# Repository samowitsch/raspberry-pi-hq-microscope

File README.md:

# Raspberry Pi HQ microscope

> Current work in progress. Feel free to contribute 😉

## Table of Contents

- [Raspberry Pi HQ microscope](#raspberry-pi-hq-microscope)
  - [Table of Contents](#table-of-contents)
  - [Preface](#preface)
  - [PCB adapter or mount between RPI 3A+ and RPI HQ camera](#pcb-adapter-or-mount-between-rpi-3a-and-rpi-hq-camera)
    - [PCB images](#pcb-images)
    - [Available buttons](#available-buttons)
  - [BOM](#bom)
  - [Software](#software)
    - [SD Card](#sd-card)
    - [Install needed packages](#install-needed-packages)
    - [Cronjobs](#cronjobs)
      - [list running cronjobs](#list-running-cronjobs)
      - [stop running cronjonb process](#stop-running-cronjonb-process)
    - [Python](#python)
  - [Links to other projects or resources](#links-to-other-projects-or-resources)
  - [Videos](#videos)
  - [more pictures](#more-pictures)

## Preface

A small project to build a custom electro microscope based on a Raspberr Pi 3A+ and Raspberry HQ camera. 
But why a 3A+? Because of current delivery problems. The 3A+ has also a normal HDMI port and not such an
fiddly diddly micro hdmi port 😜 Also the form factor and the geekworm case is a good choice.
In fact that it based on a Raspberry Pi it can be modified in any direction.

|                        |                        |
| ---------------------- | ---------------------- |
|  |  |
|  |  |

## PCB adapter or mount between RPI 3A+ and RPI HQ camera

The [pcb](pcb/README.md) acts as mounting adapter between the Raspberry Pi 3A+ and the Raspberry Pi HQ Camera. 
It has also 5 buttons that can be used to add custom functions with python.

### PCB images

| Front                             | Back                             |
| --------------------------------- | -------------------------------- |
|  |  |

### Available buttons

| Button | GPIO | Function              |
| ------ | ---- | --------------------- |
| 1      | 17   | select mode/option    |
| 2      | 27   | increase option value |
| 3      | 22   | decrease option value |
| 4      | 19   | capture photo         |
| 5      | 26   | shutdown raspi        |

## BOM

| Part                                                | Quantity     | Description                                                    |
| --------------------------------------------------- | :----------- | -------------------------------------------------------------- |
|                  | 1            | Raspberry Pi 3A+                                               |
|    | 1            | [Geekworm Raspberry pi case](http://wiki.geekworm.com/P88)     |
|                | 1            | Raspberry Pi HQ camera                                         |
|             | 1            | camera cable 6 cm                                              |
|  | 1            | 180x zoom objective with c-mount                               |
|             | 1            | 0.5x barlow lens                                               |
|               | 1            | LED ring light                                                 |
|             | 1            | Heavy duty stand                                               |
|              | 1 (optional) | HDMI 90° adapter                                               |
|                         | 1 (optional) | [spacer](spacer/README.md) for the heavy duty stand            |
|              | 1 (optional) | USB Wifi dongle **(optional for "better" wifi connectivity)**  |
|                    | 1 (optional) | [pcb](pcb/README.md) **(optional. depending to your needs.)**                       |
|     | 1 (optional) | header female 2x20 pin **(optional. depending to your needs.)** |
|                  | 5 (optional) | push button 6x6 **(optional. depending to your needs.)**       |

## Software

### SD Card

Prepare Sd-Card with Raspberry Pi OS Lite 32 bit image as usual described in a lot of places in web with [balenaEtcher](https://www.balena.io/etcher?ref=etcher_footer) or similar tool. 
64 bit version of Raspberry Pi OS is not working because needed ```libmmal``` is not available for aarch64.

### Install needed packages

```bash
sudo apt install python3-pip
sudo apt install python3-picamera

pip install picamera
```

### Cronjobs

Starting needed software with crontab on boot. Can vary depending to custom needs. Use ```crontab -e``` to edit the cron jobs.

```
# start simple preview to hdmi output
#@reboot libcamera-still -t 0 --width 1920 --height 1080 --rotation 180 -o current.jpg

# start python script. path to user home can vary in your case
#@reboot sudo python /home/micro/shutdown.py
@reboot sudo python /home/micro/advanced.py
```

#### list running cronjobs

```bash
pstree -apl `pidof cron`

or 

ps aux |grep "/home/micro/advanced.py"

or

ps -o pid,sess,cmd afx | egrep -A20 "( |/)cron( -f)?$"
```

#### stop running cronjonb process

```bash
# stopping process
pkill -s [pid]

#example
pkill -s 424
```

### Python

Scripts for use with cronjob. Place it in the home folder.

* [Simple shutdown only script](src/shutdown.py)
* [Advanced script](src/advanced.py)

## Links to other projects or resources

* [Thingiverse: Pi Mocroscope](https://www.thingiverse.com/thing:3920261)
* [hackaday.io: Pi Microscope](https://hackaday.io/project/167996-pi-microscope)
* [Github: amphioxus/raspi_camera_scripts](https://github.com/raspberrypi/picamera2)
* [Github: raspberrypi/picamera2](https://github.com/amphioxus/raspi_camera_scripts)
* [element14 community: I Spy With My Digital Eye .... a Pico PI](https://community.element14.com/challenges-projects/project14/offtheshelf/b/blog/posts/i-spy-with-my-digital-eye-a-pico-pi)
* [Picamera 1.13 readthedocs](https://picamera.readthedocs.io/en/release-1.13/)
* [Picamera 2 library pdf](https://datasheets.raspberrypi.com/camera/picamera2-manual.pdf)
* [Geekworm Raspberry pi case](http://wiki.geekworm.com/P88)

## Videos

* [YT Video Part 1](https://www.youtube.com/watch?v=33pAQVsLFqw&ab_channel=daSamo123)
* [YT Video Part 2](https://www.youtube.com/watch?v=zNRziszGEiE&ab_channel=daSamo123)

## more pictures

[More pictures](README-more-pics.md)

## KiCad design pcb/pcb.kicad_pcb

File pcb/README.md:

# PCB adapter or mount between RPI and RPI HQ camera

For more details see. KiCad files.

| Front                                      | Back                                      |
| ------------------------------------------ | ----------------------------------------- |
|  |  |

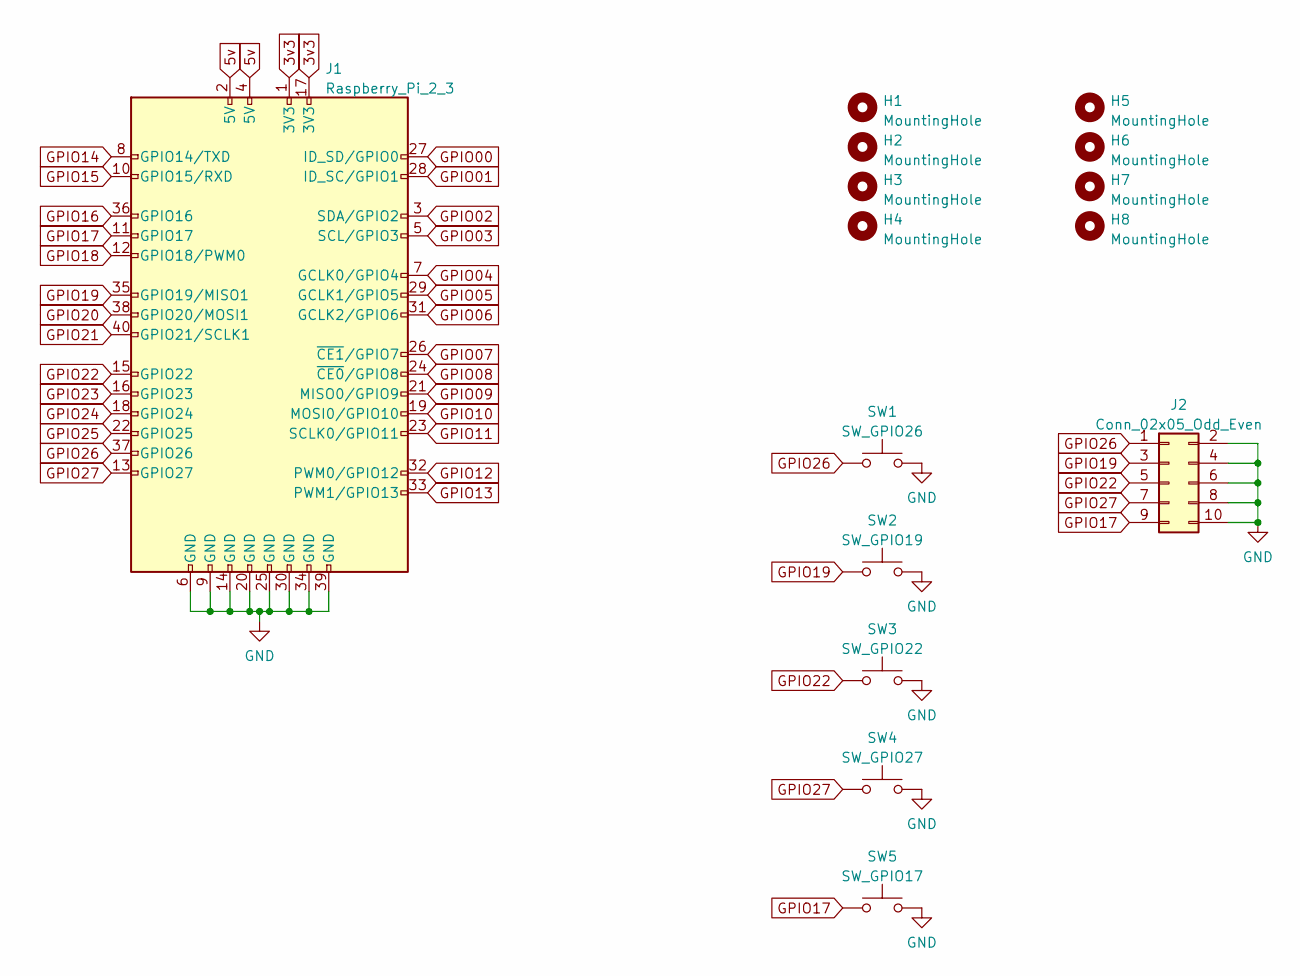
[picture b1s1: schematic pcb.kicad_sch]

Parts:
H1, H2, H3, H4: MountingHole; MountingHole_2.7mm_M2.5_Pad_Via
H5, H6, H7, H8: MountingHole; MountingHole_2.7mm
J1: Raspberry_Pi_2_3; PinSocket_2x20_P2.54mm_Vertical
J2: Conn_02x05_Odd_Even; PinHeader_2x05_P2.54mm_Vertical
SW1: SW_GPIO26; SW_PUSH_6mm_H5mm
SW2: SW_GPIO19; SW_PUSH_6mm_H5mm
SW3: SW_GPIO22; SW_PUSH_6mm_H5mm
SW4: SW_GPIO27; SW_PUSH_6mm_H5mm
SW5: SW_GPIO17; SW_PUSH_6mm_H5mm

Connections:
3v3: J1.1 (3V3), J1.17 (3V3)
5v: J1.2 (5V), J1.4 (5V)
GND: J1.6 (GND), J1.9 (GND), J1.14 (GND), J1.20 (GND), J1.25 (GND), J1.30 (GND), J1.34 (GND), J1.39 (GND), J2.2, J2.4, J2.6, J2.8, J2.10, SW1.2, SW2.2, SW3.2, SW4.2, SW5.2
GPIO00: J1.27 (ID_SD/GPIO0)
GPIO01: J1.28 (ID_SC/GPIO1)
GPIO02: J1.3 (SDA/GPIO2)
GPIO03: J1.5 (SCL/GPIO3)
GPIO04: J1.7 (GCLK0/GPIO4)
GPIO05: J1.29 (GCLK1/GPIO5)
GPIO06: J1.31 (GCLK2/GPIO6)
GPIO07: J1.26 (~CE1/GPIO7)
GPIO08: J1.24 (~CE0/GPIO8)
GPIO09: J1.21 (MISO0/GPIO9)
GPIO10: J1.19 (MOSI0/GPIO10)
GPIO11: J1.23 (SCLK0/GPIO11)
GPIO12: J1.32 (PWM0/GPIO12)
GPIO13: J1.33 (PWM1/GPIO13)
GPIO14: J1.8 (GPIO14/TXD)
GPIO15: J1.10 (GPIO15/RXD)
GPIO16: J1.36 (GPIO16)
GPIO17: J1.11 (GPIO17), J2.9, SW5.1
GPIO18: J1.12 (GPIO18/PWM0)
GPIO19: J1.35 (GPIO19/MISO1), J2.3, SW2.1
GPIO20: J1.38 (GPIO20/MOSI1)
GPIO21: J1.40 (GPIO21/SCLK1)
GPIO22: J1.15 (GPIO22), J2.5, SW3.1
GPIO23: J1.16 (GPIO23)
GPIO24: J1.18 (GPIO24)
GPIO25: J1.22 (GPIO25)
GPIO26: J1.37 (GPIO26), J2.1, SW1.1
GPIO27: J1.13 (GPIO27), J2.7, SW4.1

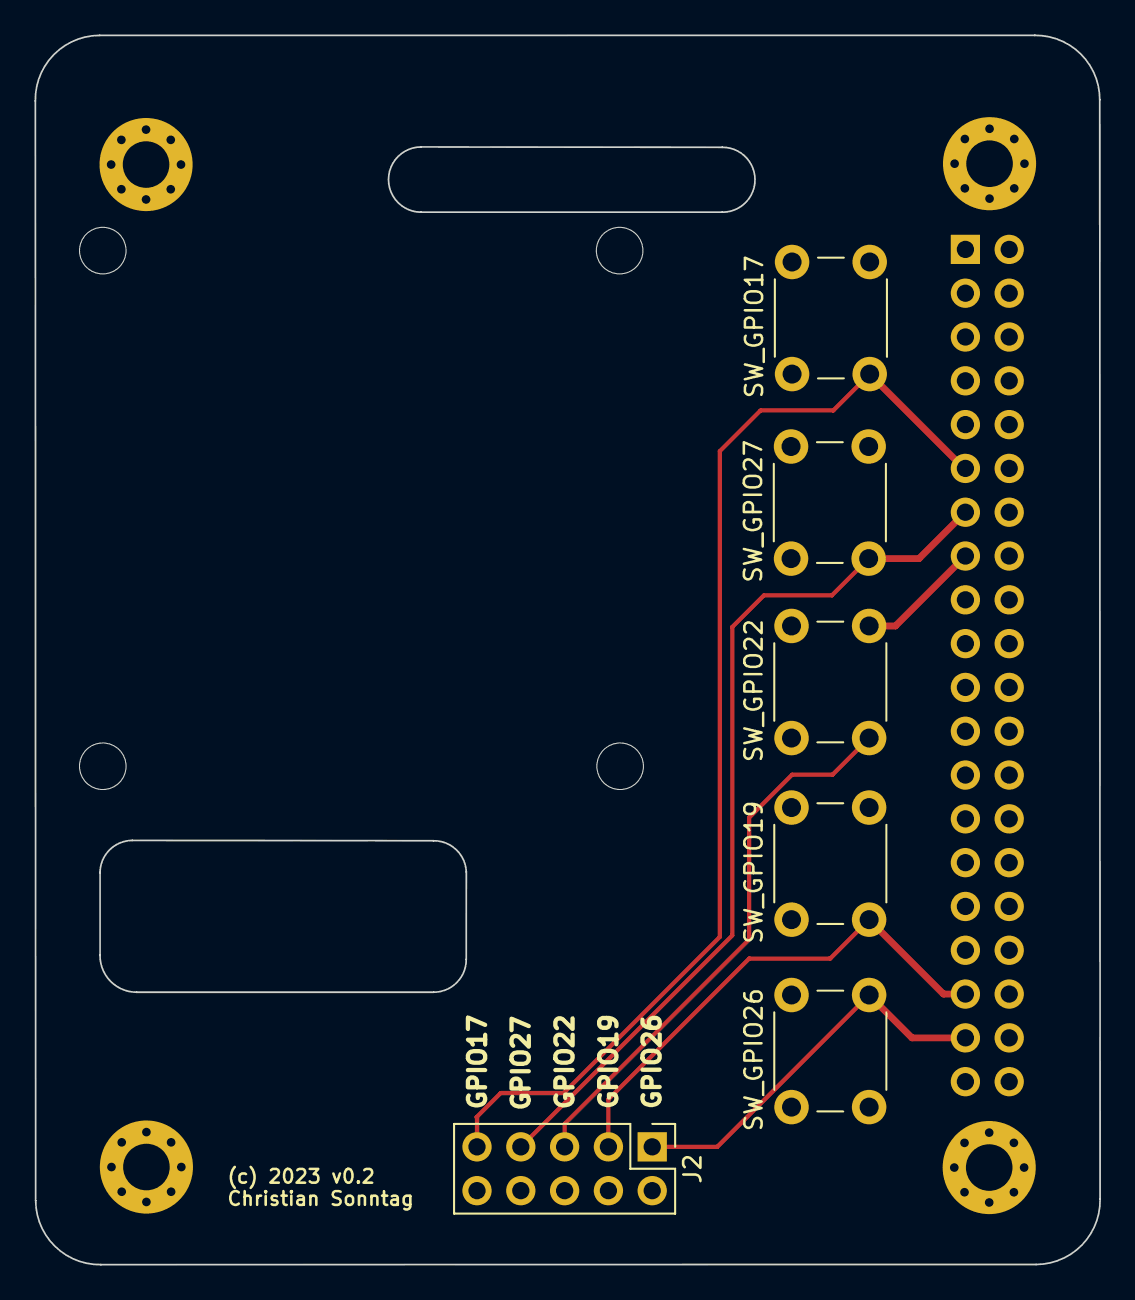
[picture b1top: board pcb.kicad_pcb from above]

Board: 2 copper layers, 61.7 x 71.3 mm, 15 parts (1 on the bottom side), 8 nets.

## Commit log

2023-01-22 refactor time object to capture placeholder
2023-01-22 changed README
2023-01-22 Revert "refactor time object to capture placeholder" It seems placeholder works only with capture_continuous ;-(
    This reverts commit c0ef082705d468f20181cc083df675ff02a56d62.
2023-01-22 add some note about running cronjob processes and how to stop then
2023-01-22 change path to capture photos to
2023-01-22 change button mapping. use button in front to capture images.
2023-01-22 fix/improve filename
2023-01-22 add additional pinheader as alternative to button switches
2023-01-22 Add Full-HD overlay.png. Change Image option to RGBA
2023-01-22 add initial Makefile
2023-01-31 README adaptiona
2023-03-11 Readme adaptions. Added more pictures.
2024-06-24 fix typo
2024-07-20 change overlay text
2024-07-20 update link section
2024-07-20 add video links
2024-07-20 overlay text adaption
2025-09-26 add shrinked zipped image file. configure git lfs.

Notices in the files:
pcb/pcb.kicad_pcb:
(c) 2023 v0.2
